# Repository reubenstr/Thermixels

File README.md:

# Thermixels

Pixel made from heat.

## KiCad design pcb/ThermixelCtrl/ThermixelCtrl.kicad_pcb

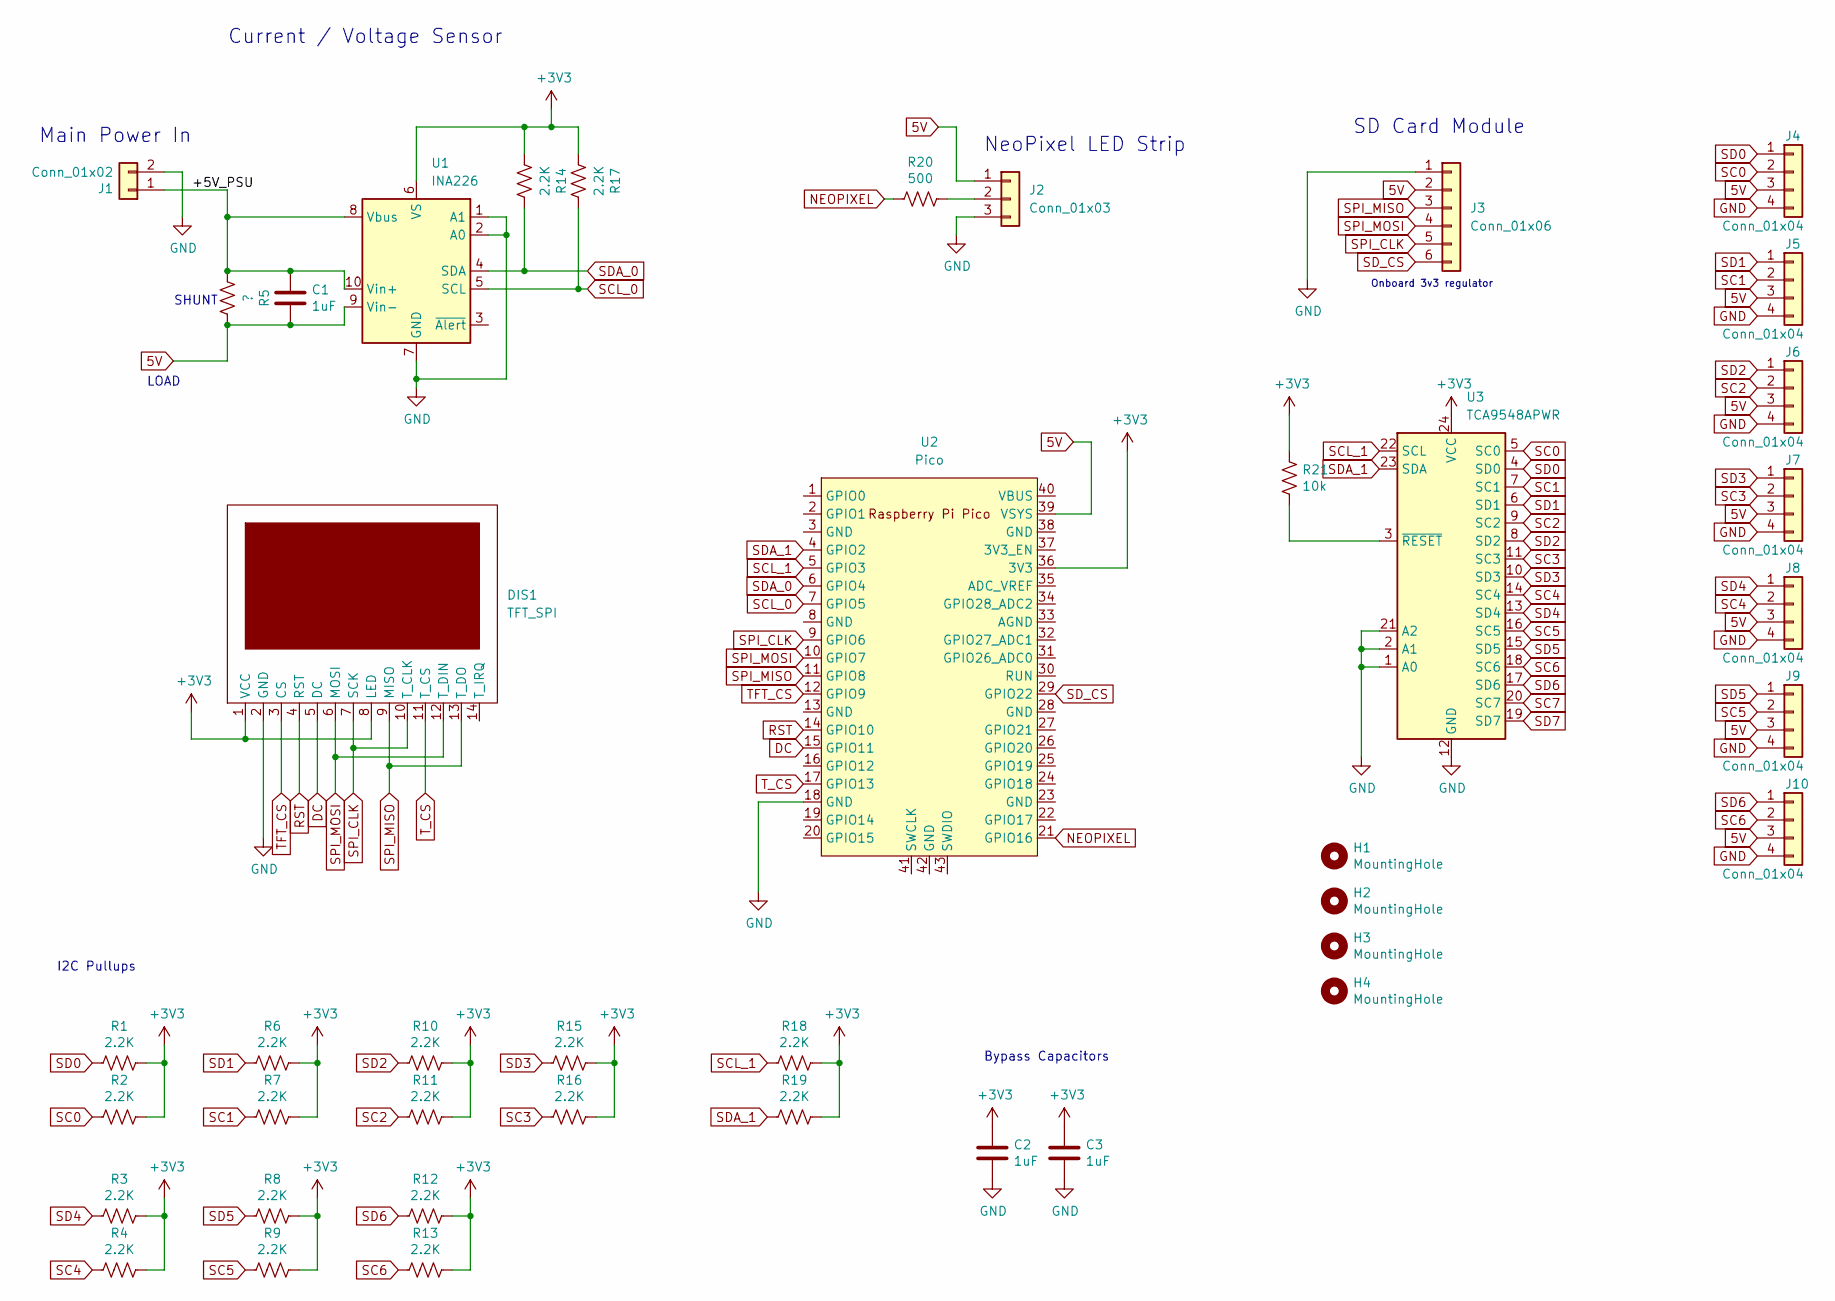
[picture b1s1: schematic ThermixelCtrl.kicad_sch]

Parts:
C1, C2, C3: 1uF; C_0805_2012Metric_Pad1.18x1.45mm_HandSolder
DIS1: TFT_SPI
H1, H2, H3, H4: MountingHole; MountingHole_3.2mm_M3
J1: Conn_01x02; TerminalBlock_bornier-2_P5.08mm
J2: Conn_01x03; PinHeader_1x03_P2.54mm_Horizontal
J3: Conn_01x06; PinHeader_1x06_P2.54mm_Horizontal
J4, J5, J6, J7, J8, J9, J10: Conn_01x04; PinHeader_1x04_P2.54mm_Horizontal
R1, R2, R3, R4, R6, R7, R8, R9, R10, R11, R12, R13, R14, R15, R16, R17, R18, R19: 2.2K; R_0805_2012Metric_Pad1.20x1.40mm_HandSolder
R5: ?; R_2512_6332Metric_Pad1.40x3.35mm_HandSolder
R20: 500; R_0805_2012Metric_Pad1.20x1.40mm_HandSolder
R21: 10k; R_0805_2012Metric_Pad1.20x1.40mm_HandSolder
U1: INA226; VSSOP-10_3x3mm_P0.5mm
U2: Pico; RPi_Pico_SMD_TH
U3: TCA9548APWR; TSSOP-24_4.4x7.8mm_P0.65mm

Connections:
5V: C1.2, J2.1, J3.2, J4.3, J5.3, J6.3, J7.3, J8.3, J9.3, J10.3, R5.1, U1.9 (Vin-), U2.39 (VSYS)
+3V3: C2.1, C3.1, DIS1.1 (VCC), DIS1.8 (LED), R1.1, R2.1, R3.1, R4.1, R6.1, R7.1, R8.1, R9.1, R10.1, R11.1, R12.1, R13.1, R14.2, R15.1, R16.1, R17.2, R18.1, R19.1, R21.1, U1.6 (VS), U2.36 (3V3), U3.24 (VCC)
/+5V_PSU: C1.1, J1.1, R5.2, U1.8 (Vbus), U1.10 (Vin+)
DC: DIS1.5 (DC), U2.15 (GPIO11)
GND: C2.2, C3.2, DIS1.2 (GND), J1.2, J2.3, J3.1, J4.4, J5.4, J6.4, J7.4, J8.4, J9.4, J10.4, U1.1 (A1), U1.2 (A0), U1.7 (GND), U2.18 (GND), U3.1 (A0), U3.2 (A1), U3.12 (GND), U3.21 (A2)
NEOPIXEL: R20.2, U2.21 (GPIO16)
unnamed: J2.2, R20.1
unnamed: R21.2, U3.3 (~RESET)
RST: DIS1.4 (RST), U2.14 (GPIO10)
SC0: J4.2, R2.2, U3.5 (SC0)
SC1: J5.2, R7.2, U3.7 (SC1)
SC2: J6.2, R11.2, U3.9 (SC2)
SC3: J7.2, R16.2, U3.11 (SC3)
SC4: J8.2, R4.2, U3.14 (SC4)
SC5: J9.2, R9.2, U3.16 (SC5)
SC6: J10.2, R13.2, U3.18 (SC6)
SC7: U3.20 (SC7)
SCL_0: R17.1, U1.5 (SCL), U2.7 (GPIO5)
SCL_1: R18.2, U2.5 (GPIO3), U3.22 (SCL)
SD0: J4.1, R1.2, U3.4 (SD0)
SD1: J5.1, R6.2, U3.6 (SD1)
SD2: J6.1, R10.2, U3.8 (SD2)
SD3: J7.1, R15.2, U3.10 (SD3)
SD4: J8.1, R3.2, U3.13 (SD4)
SD5: J9.1, R8.2, U3.15 (SD5)
SD6: J10.1, R12.2, U3.17 (SD6)
SD7: U3.19 (SD7)
SDA_0: R14.1, U1.4 (SDA), U2.6 (GPIO4)
SDA_1: R19.2, U2.4 (GPIO2), U3.23 (SDA)
SD_CS: J3.6, U2.29 (GPIO22)
SPI_CLK: DIS1.7 (SCK), DIS1.10 (T_CLK), J3.5, U2.9 (GPIO6)
SPI_MISO: DIS1.9 (MISO), DIS1.13 (T_DO), J3.3, U2.11 (GPIO8)
SPI_MOSI: DIS1.6 (MOSI), DIS1.12 (T_DIN), J3.4, U2.10 (GPIO7)
TFT_CS: DIS1.3 (CS), U2.12 (GPIO9)
T_CS: DIS1.11 (T_CS), U2.17 (GPIO13)

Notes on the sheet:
SD Card Module
Current / Voltage Sensor
Main Power In
Bypass Capacitors
Onboard 3v3 regulator
LOAD
I2C Pullups
SHUNT
NeoPixel LED Strip

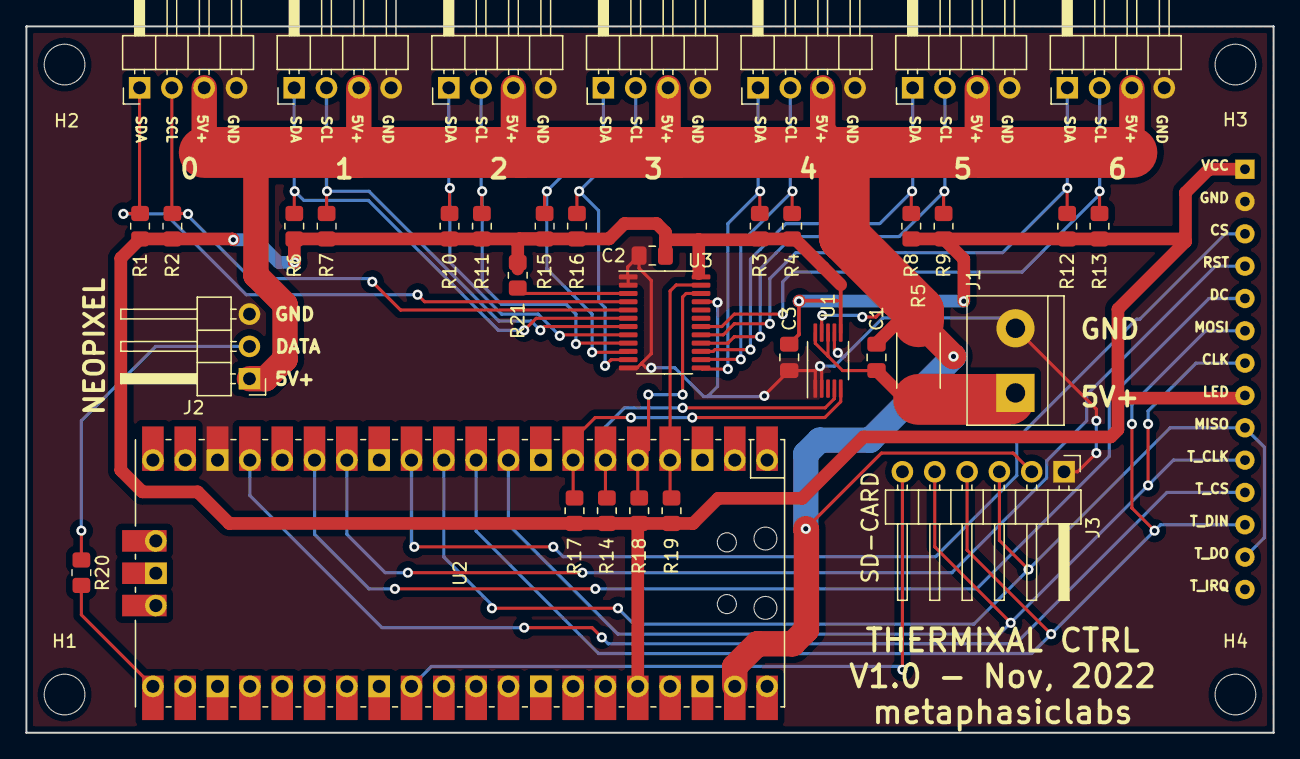
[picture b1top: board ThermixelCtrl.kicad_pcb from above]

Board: 2 copper layers, 98.0 x 55.5 mm, 42 parts (1 on the bottom side), 33 nets.

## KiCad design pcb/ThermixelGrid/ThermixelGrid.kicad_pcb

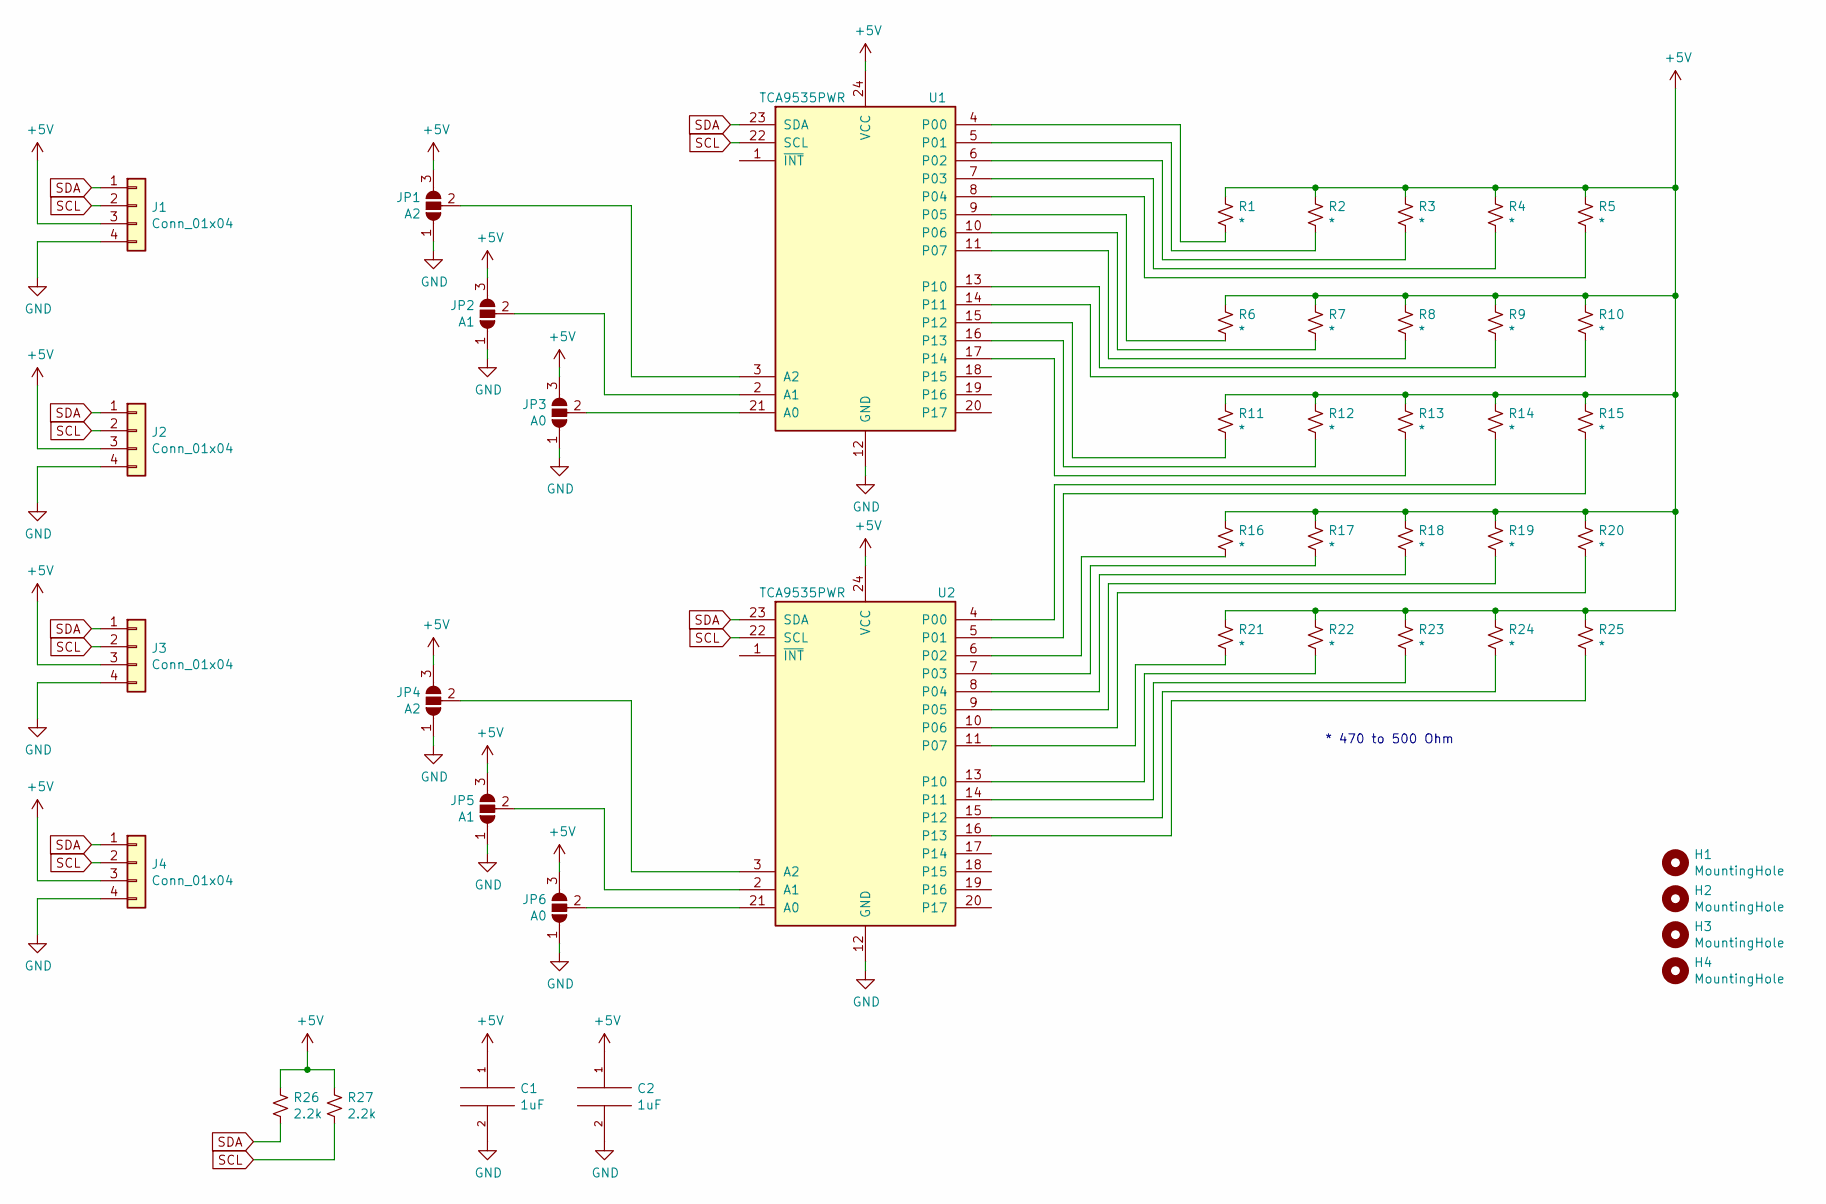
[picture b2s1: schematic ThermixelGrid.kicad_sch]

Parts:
C1, C2: 1uF; C_0805_2012Metric_Pad1.18x1.45mm_HandSolder
H1, H2, H3, H4: MountingHole; MountingHole_2.2mm_M2
J1, J2, J3, J4: Conn_01x04; conn_1x4_SMD
JP1, JP4: A2; SolderJumper-3_P1.3mm_Open_RoundedPad1.0x1.5mm
JP2, JP5: A1; SolderJumper-3_P1.3mm_Open_RoundedPad1.0x1.5mm
JP3, JP6: A0; SolderJumper-3_P1.3mm_Open_RoundedPad1.0x1.5mm
R1, R2, R3, R4, R5, R6, R7, R8, R9, R10, R11, R12, R13, R14, R15, R16, R17, R18, R19, R20, R21, R22, R23, R24, R25: *; R_2010_5025Metric
R26, R27: 2.2k; R_0805_2012Metric
U1, U2: TCA9535PWR; TSSOP-24_4.4x7.8mm_P0.65mm

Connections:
+5V: C1.1, C2.1, J1.3, J2.3, J3.3, J4.3, JP1.3 (B), JP2.3 (B), JP3.3 (B), JP4.3 (B), JP5.3 (B), JP6.3 (B), R1.1, R2.1, R3.1, R4.1, R5.1, R6.1, R7.1, R8.1, R9.1, R10.1, R11.1, R12.1, R13.1, R14.1, R15.1, R16.1, R17.1, R18.1, R19.1, R20.1, R21.1, R22.1, R23.1, R24.1, R25.1, R26.1, R27.1, U1.24 (VCC), U2.24 (VCC)
GND: C1.2, C2.2, J1.4, J2.4, J3.4, J4.4, JP1.1 (A), JP2.1 (A), JP3.1 (A), JP4.1 (A), JP5.1 (A), JP6.1 (A), U1.12 (GND), U2.12 (GND)
unnamed: JP1.2 (C), U1.3 (A2)
unnamed: JP2.2 (C), U1.2 (A1)
unnamed: JP3.2 (C), U1.21 (A0)
unnamed: JP4.2 (C), U2.3 (A2)
unnamed: JP5.2 (C), U2.2 (A1)
unnamed: JP6.2 (C), U2.21 (A0)
unnamed: R1.2, U1.4 (P00)
unnamed: R2.2, U1.5 (P01)
unnamed: R3.2, U1.6 (P02)
unnamed: R4.2, U1.7 (P03)
unnamed: R5.2, U1.8 (P04)
unnamed: R6.2, U1.9 (P05)
unnamed: R7.2, U1.10 (P06)
unnamed: R8.2, U1.11 (P07)
unnamed: R9.2, U1.13 (P10)
unnamed: R10.2, U1.14 (P11)
unnamed: R11.2, U1.15 (P12)
unnamed: R12.2, U1.16 (P13)
unnamed: R13.2, U1.17 (P14)
unnamed: R14.2, U2.4 (P00)
unnamed: R15.2, U2.5 (P01)
unnamed: R16.2, U2.6 (P02)
unnamed: R17.2, U2.7 (P03)
unnamed: R18.2, U2.8 (P04)
unnamed: R19.2, U2.9 (P05)
unnamed: R20.2, U2.10 (P06)
unnamed: R21.2, U2.11 (P07)
unnamed: R22.2, U2.13 (P10)
unnamed: R23.2, U2.14 (P11)
unnamed: R24.2, U2.15 (P12)
unnamed: R25.2, U2.16 (P13)
SCL: J1.2, J2.2, J3.2, J4.2, R27.2, U1.22 (SCL), U2.22 (SCL)
SDA: J1.1, J2.1, J3.1, J4.1, R26.2, U1.23 (SDA), U2.23 (SDA)

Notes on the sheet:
* 470 to 500 Ohm

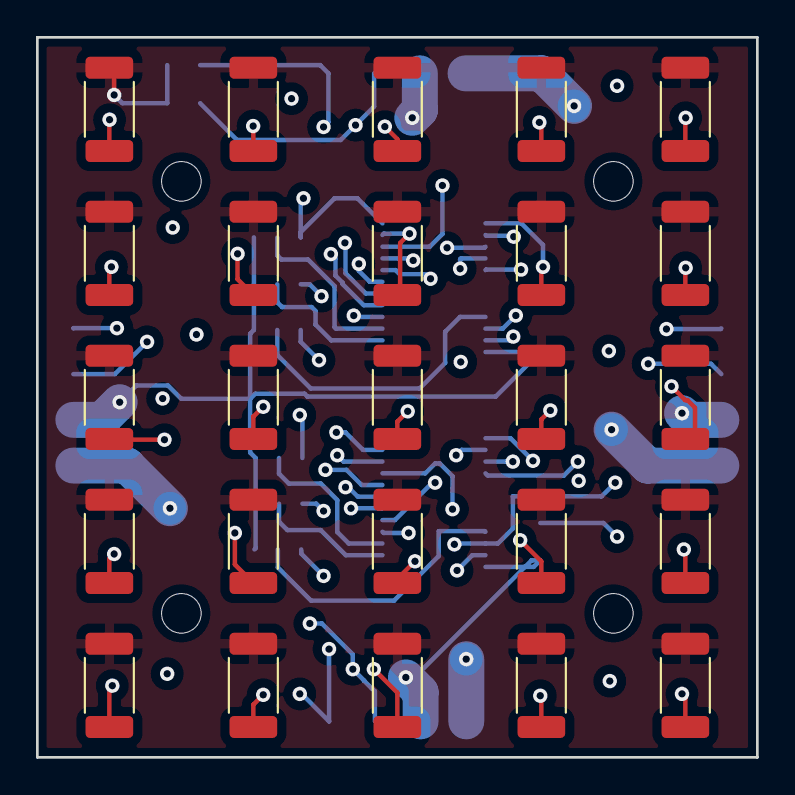
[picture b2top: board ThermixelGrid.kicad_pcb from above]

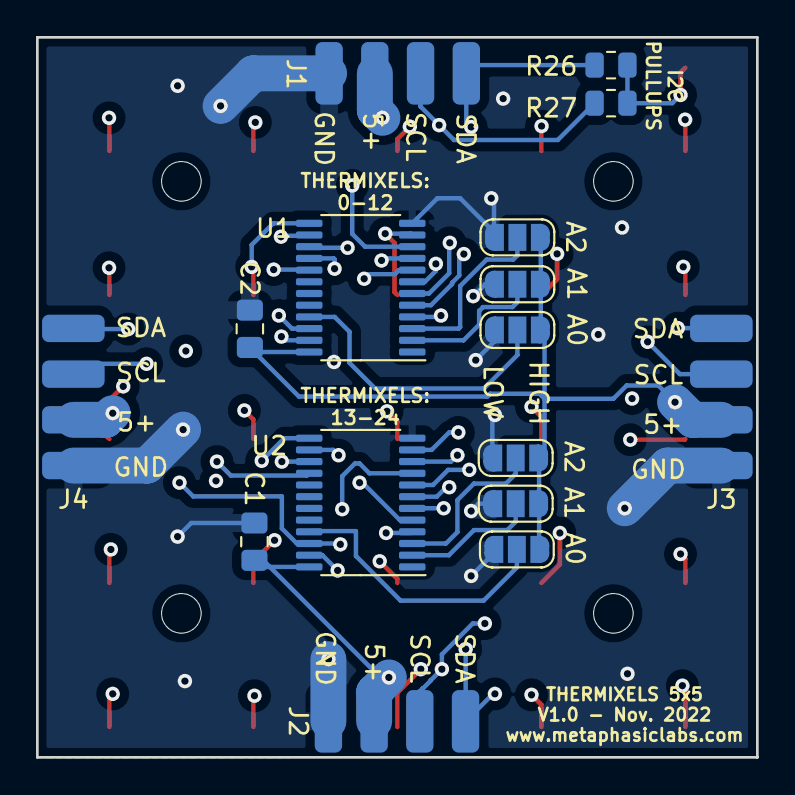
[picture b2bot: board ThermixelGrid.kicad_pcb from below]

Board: 4 copper layers, 40.0 x 40.0 mm, 45 parts (16 on the bottom side), 35 nets.

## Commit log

2024-07-07 first, post project completion
2024-07-07 upload images
2024-07-07 readme update
